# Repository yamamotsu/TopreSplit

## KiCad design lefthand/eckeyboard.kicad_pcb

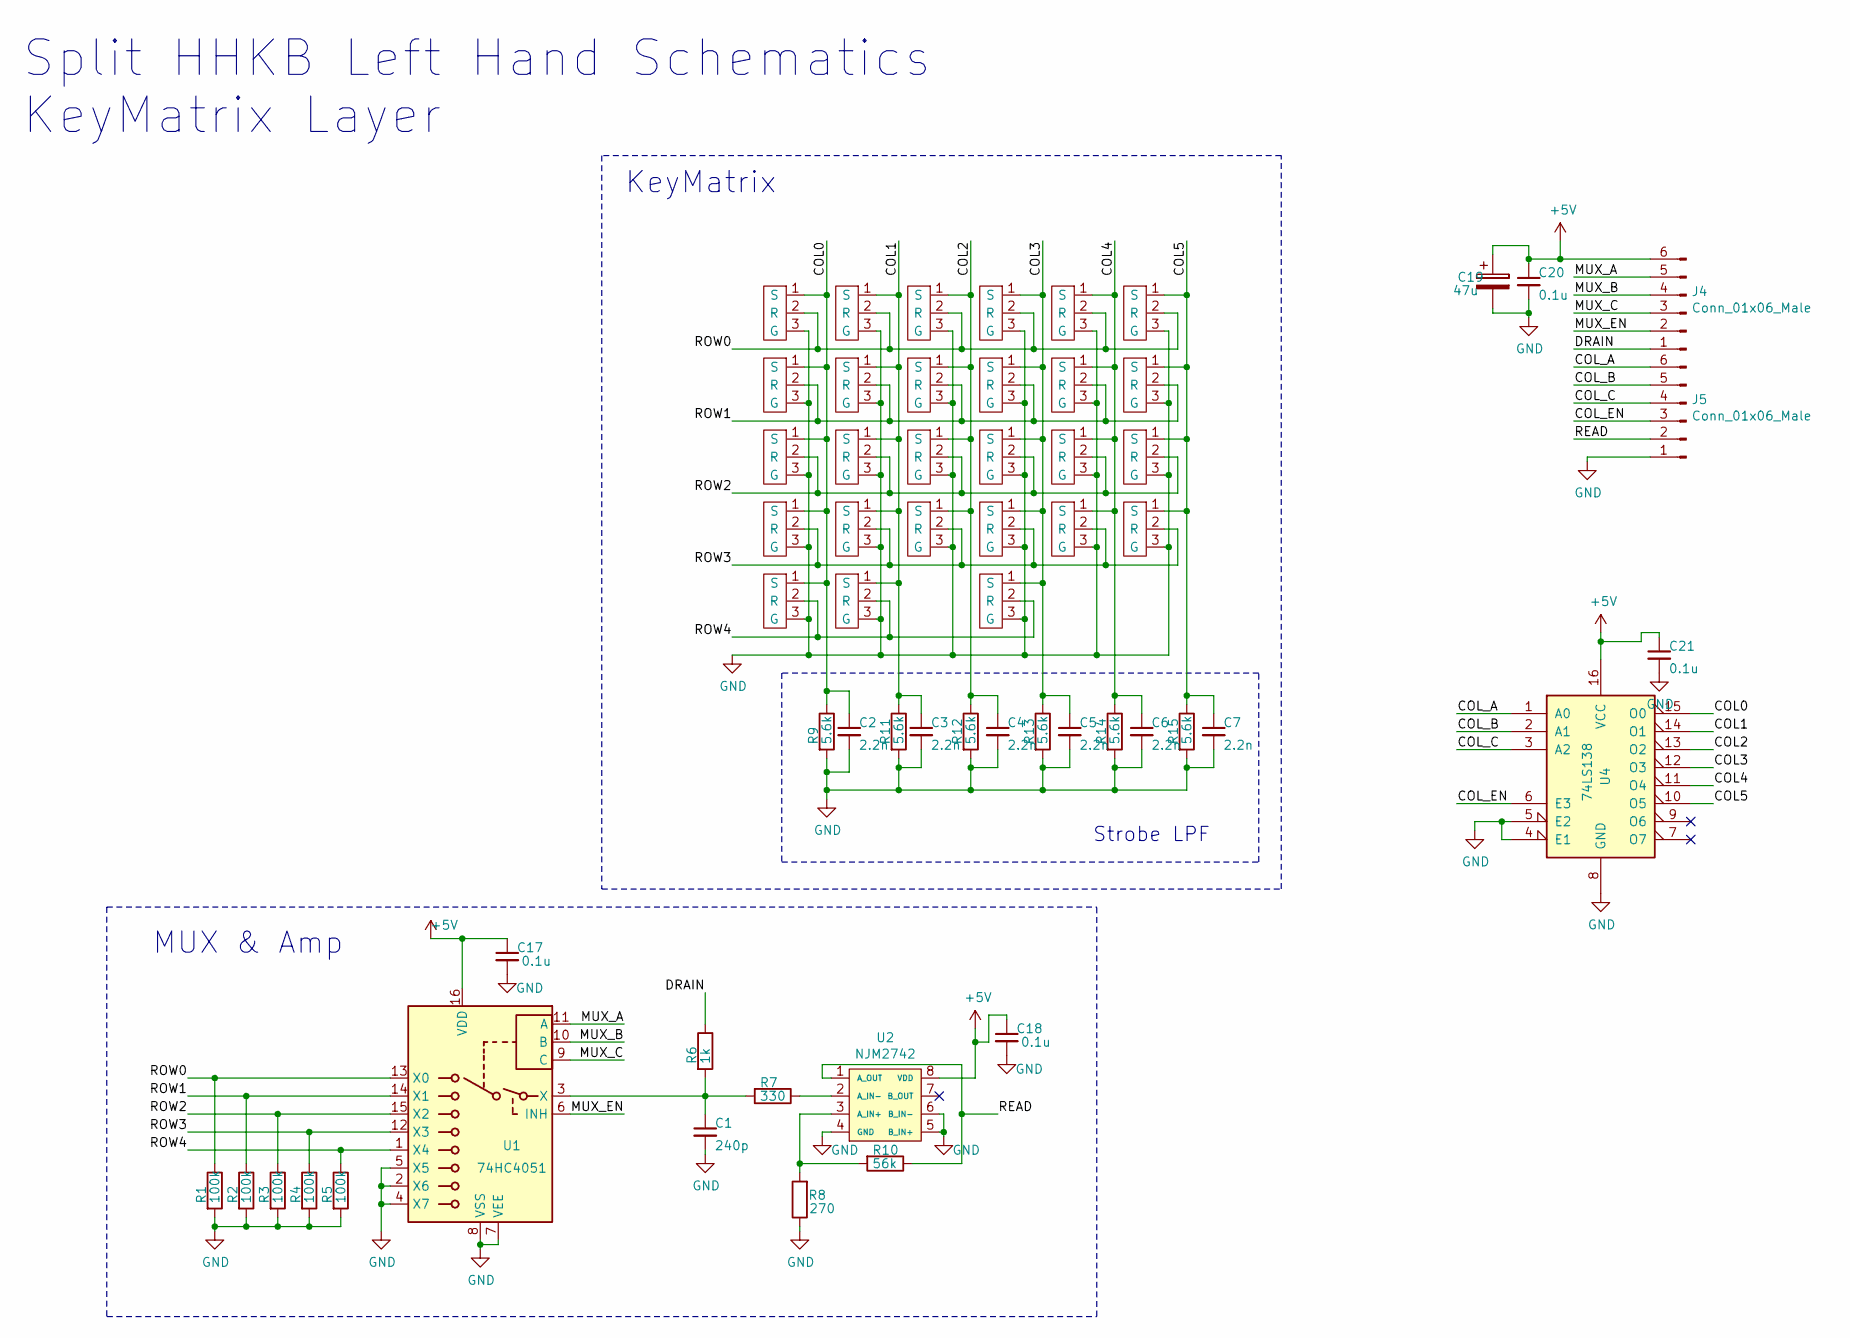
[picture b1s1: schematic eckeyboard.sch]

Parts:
C1: 240p; C_0603_1608Metric_Pad1.05x0.95mm_HandSolder
C2, C3, C4, C5, C6, C7: 2.2n; C_0603_1608Metric_Pad1.05x0.95mm_HandSolder
C17, C18, C20, C21: 0.1u; C_0603_1608Metric_Pad1.05x0.95mm_HandSolder
C19: 47u; CP_Elec_6.3x5.4_Nichicon
J4, J5: Conn_01x06_Male; ZH_6P_Horizontal
R1, R2, R3, R4, R5: 100k; R_0603_1608Metric_Pad1.05x0.95mm_HandSolder
R6: 1k; R_0603_1608Metric_Pad1.05x0.95mm_HandSolder
R7: 330; R_0603_1608Metric_Pad1.05x0.95mm_HandSolder
R8: 270; R_0603_1608Metric_Pad1.05x0.95mm_HandSolder
R9, R11, R12, R13, R14, R15: 5.6k; R_0603_1608Metric_Pad1.05x0.95mm_HandSolder
R10: 56k; R_0603_1608Metric_Pad1.05x0.95mm_HandSolder
TP1, TP2, TP3, TP4, TP5, TP6, TP7, TP8, TP9, TP10, TP11, TP12, TP13, TP14, TP15, TP16, TP17, TP18, TP19, TP20, TP21, TP22, TP23, TP24, TP25, TP26, TP27: ToprePad
U1: 74HC4051; SOP-16_4.4x10.4mm_P1.27mm
U2: NJM2742; SO-8_5.3x6.2mm_P1.27mm
U4: 74LS138; DIP-16_W7.62mm_Socket_LongPads

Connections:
+5V: C17.1, C18.1, C19.1, C20.1, C21.1, J4.6, U1.16 (VDD), U2.8 (VDD), U4.16 (VCC)
/COL0: C2.1, R9.1, TP1.1 (S), TP2.1 (S), TP3.1 (S), TP10.1 (S), TP11.1 (S), U4.15 (O0)
/COL1: C3.1, R11.1, TP4.1 (S), TP5.1 (S), TP6.1 (S), TP12.1 (S), TP13.1 (S), U4.14 (O1)
/COL2: C4.1, R12.1, TP7.1 (S), TP8.1 (S), TP9.1 (S), TP14.1 (S), U4.13 (O2)
/COL3: C5.1, R13.1, TP15.1 (S), TP16.1 (S), TP17.1 (S), TP18.1 (S), TP19.1 (S), U4.12 (O3)
/COL4: C6.1, R14.1, TP20.1 (S), TP21.1 (S), TP22.1 (S), TP23.1 (S), U4.11 (O4)
/COL5: C7.1, R15.1, TP24.1 (S), TP25.1 (S), TP26.1 (S), TP27.1 (S), U4.10 (O5)
/COL_A: J5.6, U4.1 (A0)
/COL_B: J5.5, U4.2 (A1)
/COL_C: J5.4, U4.3 (A2)
/COL_EN: J5.3, U4.6 (E3)
/DRAIN: J4.1, R6.1
/MUX_A: J4.5, U1.11 (A)
/MUX_B: J4.4, U1.10 (B)
/MUX_C: J4.3, U1.9 (C)
/MUX_EN: J4.2, U1.6 (INH)
/READ: J5.2, R10.1, U2.1 (A_OUT)
/ROW0: R1.1, TP1.2 (R), TP4.2 (R), TP7.2 (R), TP15.2 (R), TP20.2 (R), TP24.2 (R), U1.13 (X0)
/ROW1: R2.1, TP2.2 (R), TP5.2 (R), TP8.2 (R), TP16.2 (R), TP21.2 (R), TP25.2 (R), U1.14 (X1)
/ROW2: R3.1, TP3.2 (R), TP6.2 (R), TP9.2 (R), TP17.2 (R), TP22.2 (R), TP26.2 (R), U1.15 (X2)
/ROW3: R4.1, TP10.2 (R), TP12.2 (R), TP14.2 (R), TP18.2 (R), TP23.2 (R), TP27.2 (R), U1.12 (X3)
/ROW4: R5.1, TP11.2 (R), TP13.2 (R), TP19.2 (R), U1.1 (X4)
GND: C1.2, C2.2, C3.2, C4.2, C5.2, C6.2, C7.2, C17.2, C18.2, C19.2, C20.2, C21.2, J5.1, R1.2, R2.2, R3.2, R4.2, R5.2, R8.1, R9.2, R11.2, R12.2, R13.2, R14.2, R15.2, TP1.3 (G), TP2.3 (G), TP3.3 (G), TP4.3 (G), TP5.3 (G), TP6.3 (G), TP7.3 (G), TP8.3 (G), TP9.3 (G), TP10.3 (G), TP11.3 (G), TP12.3 (G), TP13.3 (G), TP14.3 (G), TP15.3 (G), TP16.3 (G), TP17.3 (G), TP18.3 (G), TP19.3 (G), TP20.3 (G), TP21.3 (G), TP22.3 (G), TP23.3 (G), TP24.3 (G), TP25.3 (G), TP26.3 (G), TP27.3 (G), U1.2 (X6), U1.4 (X7), U1.5 (X5), U1.7 (VEE), U1.8 (VSS), U2.4 (GND), U2.5 (B_IN+), U2.6 (B_IN-), U4.4 (E1), U4.5 (E2), U4.8 (GND)
unnamed: C1.1, R6.2, R7.2, U1.3 (X)
unnamed: R7.1, U2.2 (A_IN-)
unnamed: R8.2, R10.2, U2.3 (A_IN+)

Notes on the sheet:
Strobe LPF
Split HHKB Left Hand Schematics KeyMatrix Layer
KeyMatrix
MUX & Amp

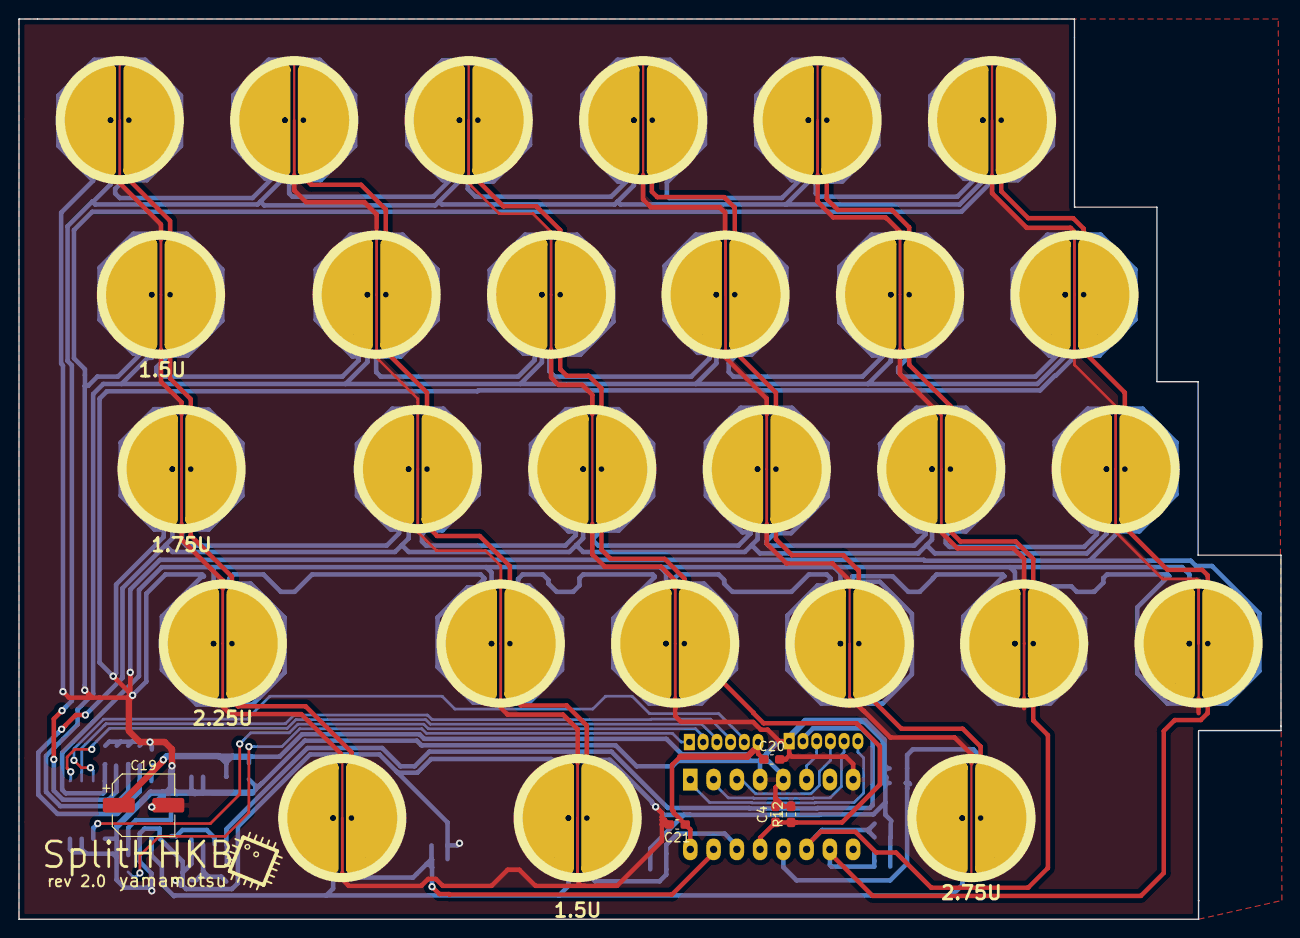
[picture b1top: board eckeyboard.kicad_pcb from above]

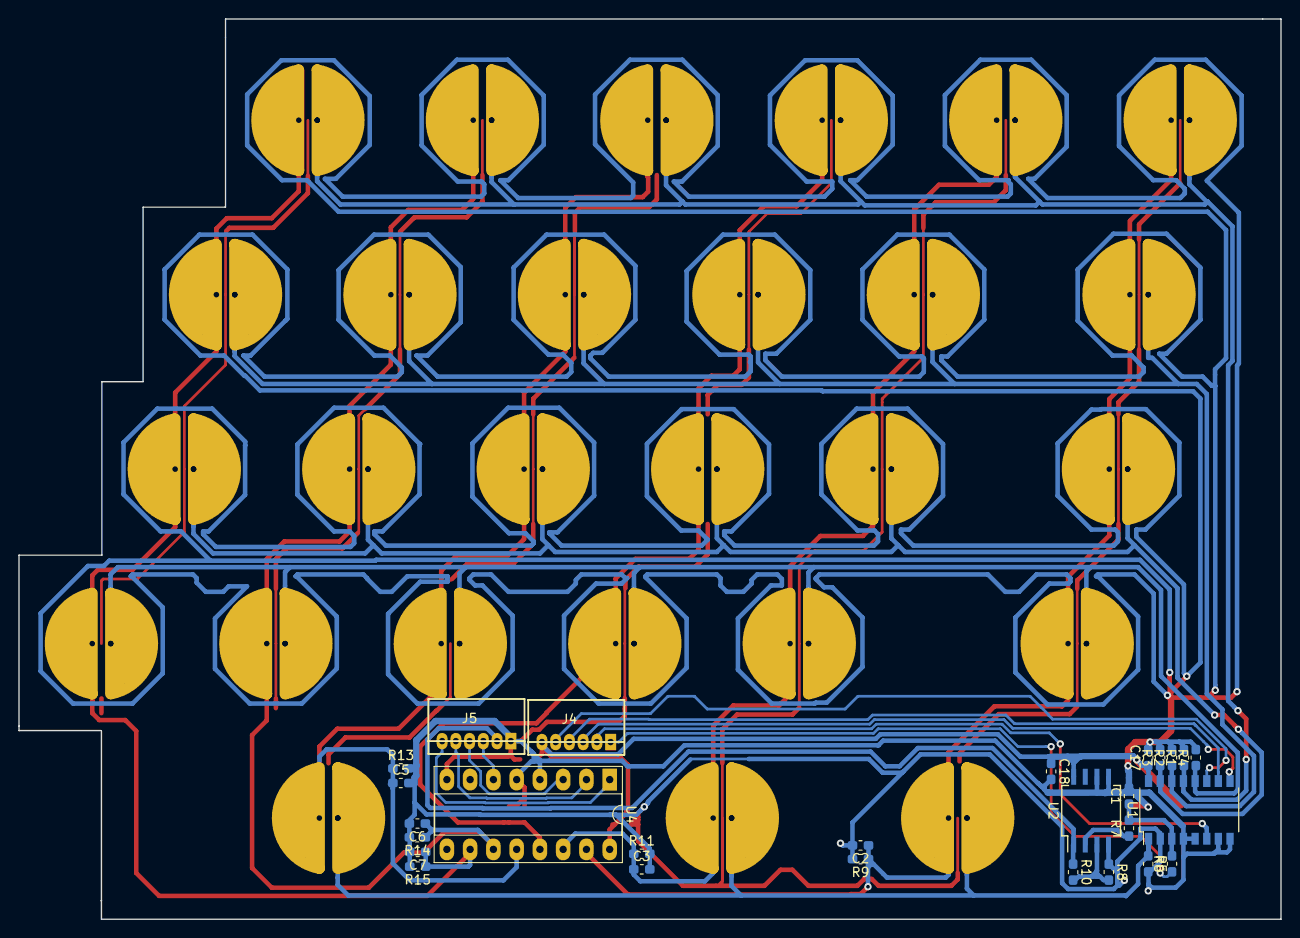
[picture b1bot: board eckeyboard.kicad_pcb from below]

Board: 2 copper layers, 137.8 x 98.3 mm, 59 parts (54 on the bottom side), 26 nets.

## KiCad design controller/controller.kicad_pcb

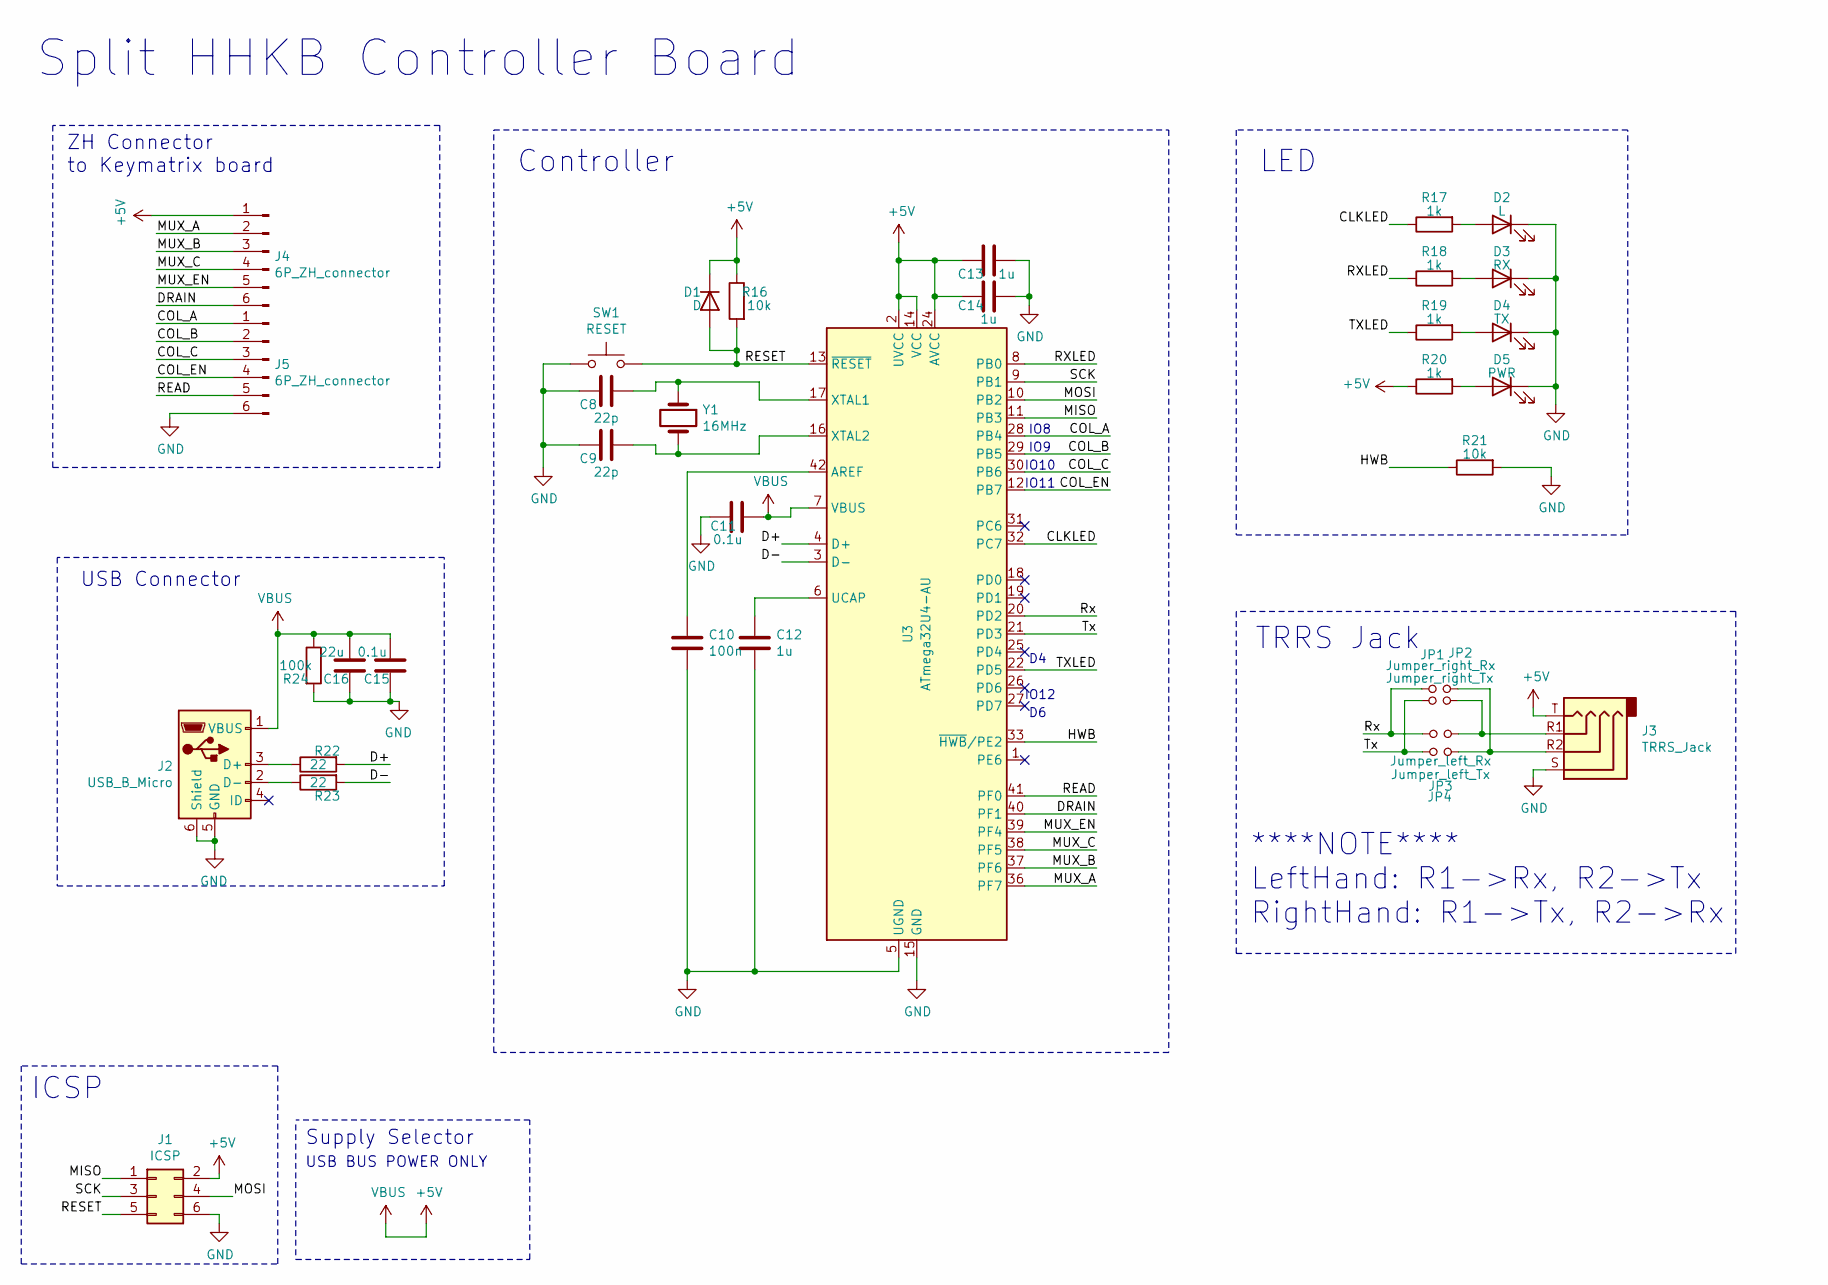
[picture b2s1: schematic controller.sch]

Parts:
C8, C9: 22p; C_0603_1608Metric_Pad1.05x0.95mm_HandSolder
C10: 100n; C_0603_1608Metric_Pad1.05x0.95mm_HandSolder
C11, C15: 0.1u; C_0603_1608Metric_Pad1.05x0.95mm_HandSolder
C12, C13, C14: 1u; C_0603_1608Metric_Pad1.05x0.95mm_HandSolder
C16: 22u; C_0603_1608Metric_Pad1.05x0.95mm_HandSolder
D1: D; D_0603_1608Metric_Pad1.05x0.95mm_HandSolder
D2: L; D_0603_1608Metric_Pad1.05x0.95mm_HandSolder
D3: RX; D_0603_1608Metric_Pad1.05x0.95mm_HandSolder
D4: TX; D_0603_1608Metric_Pad1.05x0.95mm_HandSolder
D5: PWR; D_0603_1608Metric_Pad1.05x0.95mm_HandSolder
J1: ICSP; PinHeader_2x03_P2.54mm_Vertical
J2: USB_B_Micro; USB_Micro-B_Molex_47346-0001
J3: TRRS_Jack; TRRS_jack_MJ4PP9
J6, J7: 6P_ZH_connector; ZH_6P_Horizontal
JP1: Jumper_right_Tx; soldering_jumper_W0.8_P0.2
JP2: Jumper_right_Rx; soldering_jumper_W0.8_P0.2
JP3: Jumper_left_Rx; soldering_jumper_W0.8_P0.2
JP4: Jumper_left_Tx; soldering_jumper_W0.8_P0.2
R16, R21: 10k; R_0603_1608Metric_Pad1.05x0.95mm_HandSolder
R17, R18, R19, R20: 1k; R_0603_1608Metric_Pad1.05x0.95mm_HandSolder
R22, R23: 22; R_0603_1608Metric_Pad1.05x0.95mm_HandSolder
R24: 100k; R_0603_1608Metric_Pad1.05x0.95mm_HandSolder
SW1: RESET; SW_SPST_FSMSM
U3: ATmega32U4-AU; TQFP-44_10x10mm_P0.8mm
Y1: 16MHz; Crystal_HC50_Vertical

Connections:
+5V: C11.1, C13.2, C14.2, C15.1, C16.1, D1.1 (K), J1.2, J2.1 (VBUS), J3.T, R16.1, R20.1, R24.1, U3.2 (UVCC), U3.7 (VBUS), U3.14 (VCC), U3.24 (AVCC), U3.34 (VCC), U3.44 (AVCC); also elsewhere on the board
/CLKLED: R17.1, U3.32 (PC7)
/COL_A: U3.28 (PB4); also elsewhere on the board
/COL_B: U3.29 (PB5); also elsewhere on the board
/COL_C: U3.30 (PB6); also elsewhere on the board
/COL_EN: U3.12 (PB7); also elsewhere on the board
/D+: R22.2, U3.4 (D+)
/D-: R23.2, U3.3 (D-)
/DRAIN: U3.40 (PF1); also elsewhere on the board
/HWB: R21.1, U3.33 (~HWB~/PE2)
/MISO: J1.1, U3.11 (PB3)
/MOSI: J1.4, U3.10 (PB2)
/MUX_A: U3.36 (PF7); also elsewhere on the board
/MUX_B: U3.37 (PF6); also elsewhere on the board
/MUX_C: U3.38 (PF5); also elsewhere on the board
/MUX_EN: U3.39 (PF4); also elsewhere on the board
/READ: U3.41 (PF0); also elsewhere on the board
/RESET: D1.2 (A), J1.5, R16.2, SW1.2, U3.13 (~RESET)
/RXLED: R18.1, U3.8 (PB0)
/Rx: JP1.1, JP3.1, U3.20 (PD2)
/SCK: J1.3, U3.9 (PB1)
/TXLED: R19.1, U3.22 (PD5)
/Tx: JP2.1, JP4.1, U3.21 (PD3)
GND: C8.2, C9.2, C10.2, C11.2, C12.2, C13.1, C14.1, C15.2, C16.2, D2.1 (K), D3.1 (K), D4.1 (K), D5.1 (K), J1.6, J2.5 (GND), J2.6 (Shield), J3.S, R21.2, R24.2, SW1.1, U3.5 (UGND), U3.15 (GND), U3.23 (GND), U3.35 (GND), U3.43 (GND); also elsewhere on the board
unnamed: C8.1, U3.17 (XTAL1), Y1.1
unnamed: C9.1, U3.16 (XTAL2), Y1.2
unnamed: C10.1, U3.42 (AREF)
unnamed: C12.1, U3.6 (UCAP)
unnamed: D2.2 (A), R17.2
unnamed: D3.2 (A), R18.2
unnamed: D4.2 (A), R19.2
unnamed: D5.2 (A), R20.2
unnamed: J2.2 (D-), R23.1
unnamed: J2.3 (D+), R22.1
unnamed: J3.R1, JP2.2, JP3.2
unnamed: J3.R2, JP1.2, JP4.2

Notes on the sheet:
IO12
IO8
IO9
IO10
USB BUS POWER ONLY
USB Connector
****NOTE**** LeftHand: R1->Rx, R2->Tx RightHand: R1->Tx, R2->Rx
Controller
IO11
LED
ICSP
TRRS Jack
ZH Connector to Keymatrix board
Supply Selector
Split HHKB Controller Board

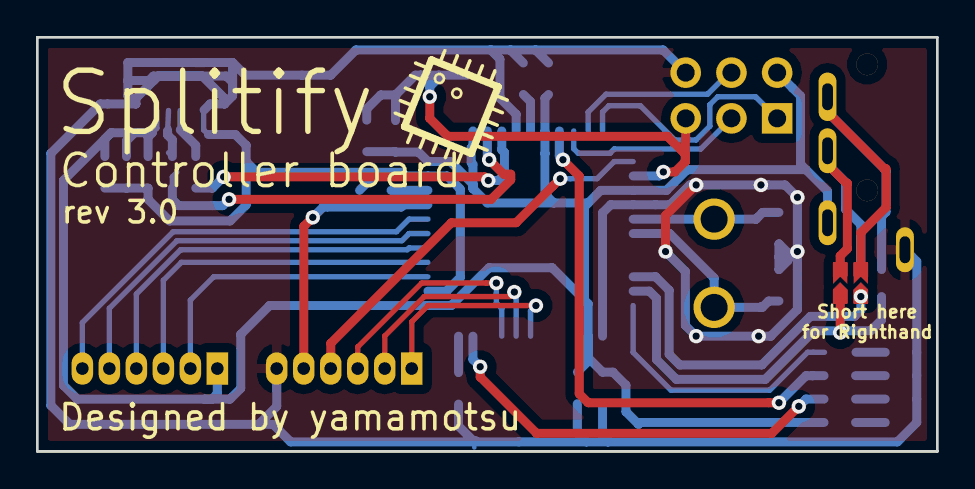
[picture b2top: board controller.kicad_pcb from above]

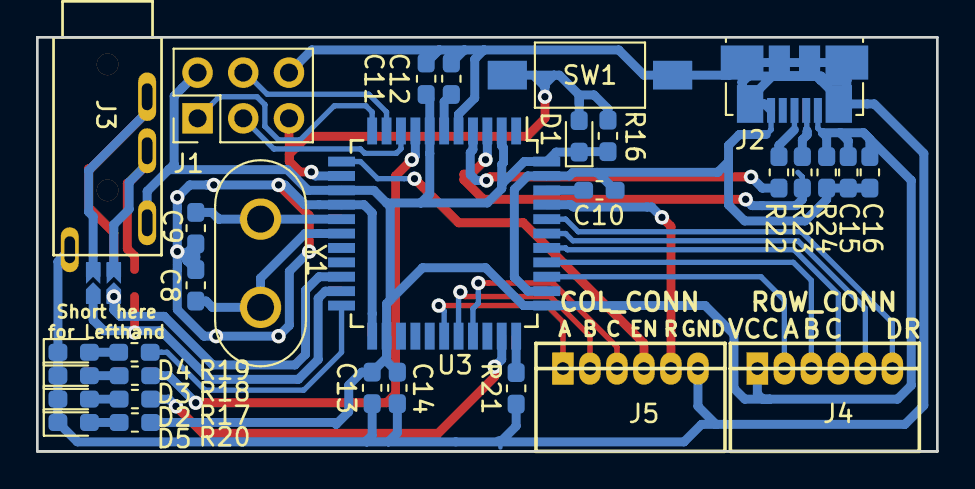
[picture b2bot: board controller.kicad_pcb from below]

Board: 2 copper layers, 50.0 x 23.0 mm, 35 parts (33 on the bottom side), 36 nets.

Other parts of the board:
J4, J5: 6P_ZH_connector; ZH_6P_Horizontal

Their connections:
+5V: J4.1; also elsewhere on the board
/COL_A: J5.1; also elsewhere on the board
/COL_B: J5.2; also elsewhere on the board
/COL_C: J5.3; also elsewhere on the board
/COL_EN: J5.4; also elsewhere on the board
/DRAIN: J4.6; also elsewhere on the board
/MUX_A: J4.2; also elsewhere on the board
/MUX_B: J4.3; also elsewhere on the board
/MUX_C: J4.4; also elsewhere on the board
/MUX_EN: J4.5; also elsewhere on the board
/READ: J5.5; also elsewhere on the board
GND: J5.6; also elsewhere on the board

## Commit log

2020-03-31 [add] first commit
2020-04-01 [add] controller board rev1.0
2020-04-01 [remove] remove controller board
2020-04-01 [move] file moved
2020-04-18 [add] controller rev2.0
2020-04-18 [add] rev 1.0
2020-05-23 [add] controller, righthand
2020-05-23 [clean] workspace cleaning
2020-05-23 [add] step files
2020-06-02 [fix] small fix
2020-06-20 [add] 3d picture, schematics pdf, pcb pdf
2020-06-20 [fix] D-/D+ flip [add] smd jumper for Tx/Rx selection
2020-06-21 [fix] mounting hole conflict
2020-06-24 [fix] MUX pin ordering fix
2020-12-22 [add] lefthand gerber
2020-12-22 [add] keytester
